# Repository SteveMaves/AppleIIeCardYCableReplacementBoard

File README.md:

# AppleIIeCardYCableReplacementBoard
This Circuit Board Design Allows FloppyEmu and a Joystick to be connected to an Apple IIe Card in a Macintosh

The purpose of this design is to replace the Apple IIe card spliter cable that is a part of the Apple IIe card 
that fit into some Macintosh computers in the early 90's.  The Y-Splitter cable is Apple Part Number 590-0703-A

Note that this circuit board only contains wiring for 5 volts.
It is suitable to run the FloppyEmu Floppy Drive Emulator device...
https://www.bigmessowires.com/floppy-emu/
but this circuit board will not power an authentic Apple drive which requires 12 volts.

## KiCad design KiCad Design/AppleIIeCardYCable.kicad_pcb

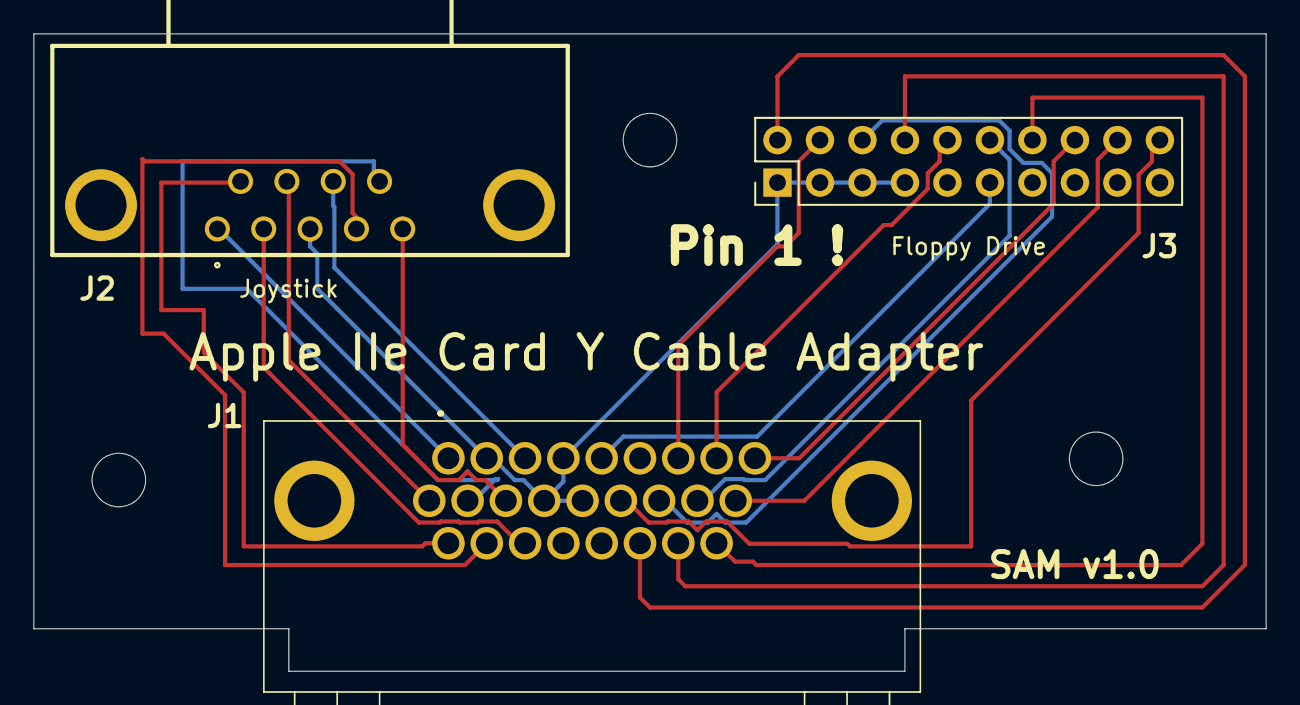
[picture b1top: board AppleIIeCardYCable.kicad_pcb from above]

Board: 2 copper layers, 73.7 x 38.1 mm, 6 parts (0 on the bottom side), 20 nets.

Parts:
H1, H2, H3: MountingHole_3.2mm_M3
J1: 10090926-P264XLF; 10090926P264XLF
J2: A-DF_09_A_KG-T2S; A-DF-09-AKG-T2S_1
J3: Conn_02x10_Odd_Even; PinHeader_2x10_P2.54mm_Vertical

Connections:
+5V: J1.5, J3.11
GND: J1.2, J1.4, J1.13, J1.14, J2.3, J3.1, J3.3, J3.5, J3.7
unnamed: J1.1, J2.1
unnamed: J1.3, J2.8
unnamed: J1.7, J3.4
unnamed: J1.8, J3.10
unnamed: J1.9, J3.16
unnamed: J1.10, J2.7
unnamed: J1.11, J2.9
unnamed: J1.12, J2.5
unnamed: J1.15, J3.20
unnamed: J1.16, J3.6
unnamed: J1.17, J3.12
unnamed: J1.18, J3.18
unnamed: J1.19, J2.6
unnamed: J1.20, J2.4
unnamed: J1.21, J2.2
unnamed: J1.24, J3.2
unnamed: J1.25, J3.8
unnamed: J1.26, J3.14
